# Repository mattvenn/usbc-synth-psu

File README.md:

# USBC Synth PSU

* uses STUSB4500 to negotiate 12v or 15v from a USBC power bank
* uses 4 [DC/DC switchers](https://www.ti.com/product/TPS56339) to supply 12, 9, 5 and 3v outputs for my various synths
* resistors can be changed to set different output voltage
* JP1 can be bridged and 12v DC/DC components not placed if power bank can supply 12v.

[PDF schematic](schematic.pdf)

[gerbers](synth-psu-2020-09-01-fab.zip)

[bom](synth-psu-bom.csv)

# Project log

For build notes, problems and fixes, please check the [project log](docs/log.md)

# Errata

* hole size is 5.3mm, should be 6 for M5 - fixed in PCB, not in gerbers

# Future improvements

* make the switcher parts snap-offable

# Resources

* proposed USBC charger: https://www.amazon.es/AUKEY-10000-mAh-Delivery-3-0-Cargador-Port%C3%A1til/dp/B07B4RQ47B/ref=sr_1_4?ascsubtag=UUacUdUnU67894YYwYg&dchild=1&keywords=AUKEY+USB+C+Power+Bank+10000mAh%2C+PD+Power+Bank+Slimline+with+18W+PD&linkCode=gs3&qid=1598631552&sr=8-4&tag=androcentr0f-21
* STUSB4500 datasheet https://www.st.com/en/interfaces-and-transceivers/stusb4500.html
* sparkfun USB PD product https://www.sparkfun.com/products/15801
* tindie USB PD product: https://github.com/oxplot/fabpide2
* sparkfun how to use their PD board: https://learn.sparkfun.com/tutorials/power-delivery-board---usb-c-qwiic-hookup-guide?_ga=2.100271642.500100063.1599656815-1406600584.1576753580

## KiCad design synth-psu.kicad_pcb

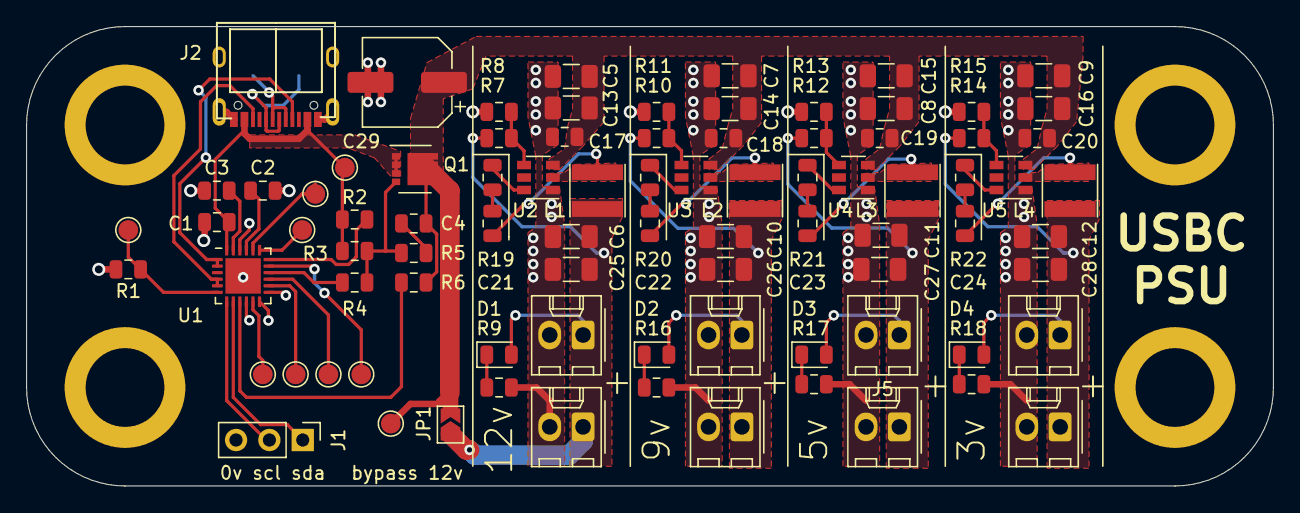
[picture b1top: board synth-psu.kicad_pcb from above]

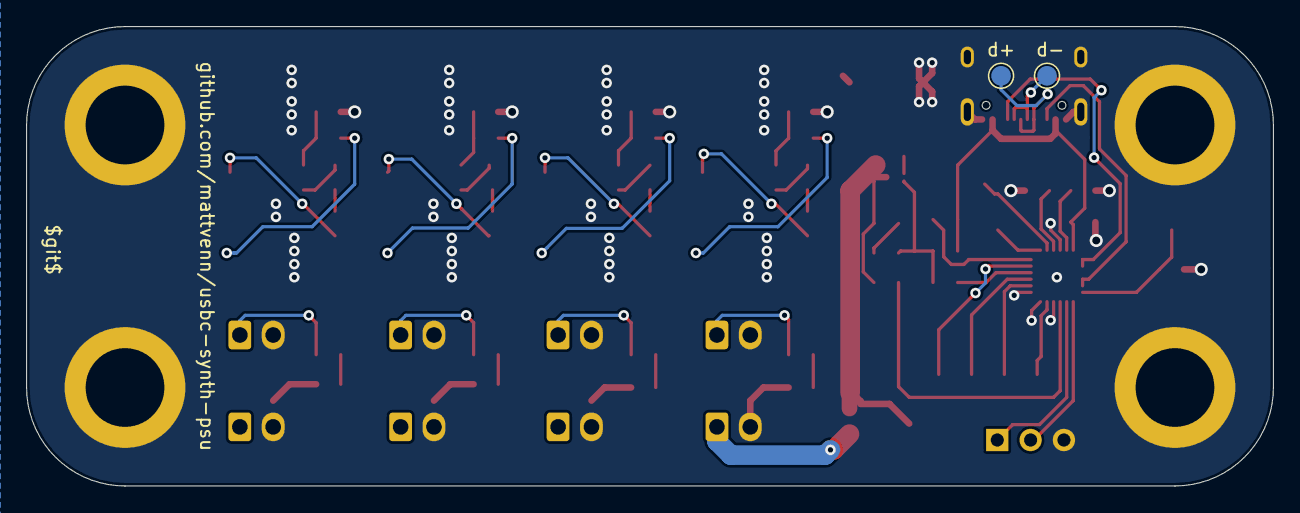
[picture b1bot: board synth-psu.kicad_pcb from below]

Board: 2 copper layers, 95.0 x 35.0 mm, 91 parts (2 on the bottom side), 47 nets.

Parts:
C1, C2, C3: 1uF; C_0805_2012Metric
C4, C17, C18, C19, C20, C21, C22, C23, C24: 100n; C_0805_2012Metric
C5, C7, C8, C9, C13, C14, C15, C16: 10u 25v; C_1206_3216Metric
C6, C10, C11, C12, C25, C26, C27, C28: 22u 16v; C_1206_3216Metric
C29: 100uf 25v; CP_Elec_6.3x5.9
D1, D2, D3, D4: LED; LED_0805_2012Metric
H1, H2, H3, H4: MountingHole_Pad; MountingHole_5.3mm_M5_DIN965_Pad
J1: Conn_01x03_Male; PinHeader_1x03_P2.54mm_Vertical
J2: USB_C_Receptacle_16pin; usb-c-16smt
J3, J4, J5, J6, J7, J8, J9, J10: Conn_01x02_Male; Molex_KK-254_AE-6410-02A_1x02_P2.54mm_Vertical
JP1: SolderJumper_2_Open; SolderJumper-2_P1.3mm_Open_TrianglePad1.0x1.5mm
L1, L2, L3, L4: 6.8uH; L_Taiyo-Yuden_NR-40xx
Q1: Q_PMOS_DSG; VSON-8_3.3x3.3mm_P0.65mm_NexFET
R1, R3, R10: 100k; R_0805_2012Metric
R2, R6: 1k; R_0805_2012Metric
R4: 22k; R_0805_2012Metric
R5, R18: 100r; R_0805_2012Metric
R7: 140k; R_0805_2012Metric
R8, R11, R13, R15: 10k; R_0805_2012Metric
R9: 660r; R_0805_2012Metric
R12: 51k; R_0805_2012Metric
R14: 27.4k; R_0805_2012Metric
R16: 470r; R_0805_2012Metric
R17: 200r; R_0805_2012Metric
R19, R20, R21, R22: 30R; R_0805_2012Metric
TP1, TP2, TP3, TP4, TP5, TP6, TP7, TP8, TP9, TP10, TP11: TestPoint; TestPoint_Pad_D1.5mm
U1: STUSB4500QTR; QFN-24-1EP_4x4mm_P0.5mm_EP2.7x2.7mm
U2, U3, U4, U5: TPS56339; SOT-23-6

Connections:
+1V2: C2.1, U1.21
+2V8: C3.1, U1.23
+3V0: C12.1, C28.1, D4.2, J6.1, J10.1, L4.2, R14.2
+5V: C11.1, C27.1, D3.2, J5.1, J9.1, L3.2, R12.2
+9V: C10.1, C26.1, D2.2, J4.1, J8.1, L2.2, R10.2
+12V: C6.1, C25.1, D1.2, J3.1, J7.1, JP1.1, L1.2, R7.2
+15V: C4.1, C5.1, C7.1, C8.1, C9.1, C13.1, C14.1, C15.1, C16.1, C17.1, C18.1, C19.1, C20.1, C29.1, JP1.2, Q1.5, R6.2, TP8.1, U2.3, U3.3, U4.3, U5.3
/cc1: J2.A5, U1.1, U1.2
/cc2: J2.B5, U1.4, U1.5
/d+: J2.A6, J2.B6, TP11.1
/d-: J2.A7, J2.B7, TP10.1
/disch: R6.1, U1.9
/scl: J1.2, U1.7
/sda: J1.1, U1.8
/sw_3: C24.2, L4.1, U5.2
/sw_5: C23.2, L3.1, U4.2
/sw_9: C22.2, L2.1, U3.2
/sw_12v: C21.2, L1.1, U2.2
/vbus_en_sink: R4.2, U1.16
/vbus_vs_disch: R2.2, U1.18
Earth: C1.2, C2.2, C3.2, C5.2, C6.2, C7.2, C8.2, C9.2, C10.2, C11.2, C12.2, C13.2, C14.2, C15.2, C16.2, C17.2, C18.2, C19.2, C20.2, C25.2, C26.2, C27.2, C28.2, C29.2, H1.1, H2.1, H3.1, H4.1, J1.3, J2.A1/B12, J2.B1/A12, J2.S1, J2.S2, J2.S3, J2.S4, J3.2, J4.2, J5.2, J6.2, J7.2, J8.2, J9.2, J10.2, R1.2, R8.1, R9.1, R11.1, R13.1, R15.1, R16.1, R17.1, R18.1, U1.10, U1.12, U1.13, U1.22, U1.25, U2.1, U3.1, U4.1, U5.1
unnamed: C4.2, R5.1
unnamed: C21.1, R19.2
unnamed: C22.1, R20.2
unnamed: C23.1, R21.2
unnamed: C24.1, R22.2
unnamed: D1.1, R9.2
unnamed: D2.1, R16.2
unnamed: D3.1, R17.2
unnamed: D4.1, R18.2
unnamed: Q1.4, R3.2, R4.1, R5.2
unnamed: R1.1, TP7.1, U1.6
unnamed: R7.1, R8.2, U2.4
unnamed: R10.1, R11.2, U3.4
unnamed: R12.1, R13.2, U4.4
unnamed: R14.1, R15.2, U5.4
unnamed: R19.1, U2.6
unnamed: R20.1, U3.6
unnamed: R21.1, U4.6
unnamed: R22.1, U5.6
unnamed: TP1.1, U1.19
unnamed: TP2.1, U1.20
unnamed: TP3.1, U1.14
unnamed: TP4.1, U1.17
unnamed: TP5.1, U1.11
unnamed: TP6.1, U1.15
VBUS: C1.1, J2.A4/B9, J2.B4/A9, Q1.1, Q1.2, Q1.3, R2.1, R3.1, TP9.1, U1.24

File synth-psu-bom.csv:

"Ref","Qnty","Value","Cmp name","Manufacturer","Partnum"
"C1, C2, C3, ","3","1uF","C","Kemet","C0805C105K3PACTU"
"C4, C17, C18, C19, C20, C21, C22, C23, C24, ","9","100n","C","Kemet","C0805C104Z3VACTU"
"C5, C7, C8, C9, C13, C14, C15, C16, ","8","10u 25v","C","Multicomp","MC1206X106K250CT"
"C6, C10, C11, C12, C25, C26, C27, C28, ","8","22u 16v","C","Kemet","C1206C226M4PACTU"
"C29, ","1","100uf 25v","CP","Panasonic","EEEFKE101XAP"
"D1, D2, D3, D4, ","4","LED","LED","Kingbright","KPT-2012EC "
"H1, H2, H3, H4, ","4","MountingHole_Pad","MountingHole_Pad","",""
"J1, ","1","Conn_01x03_Male","Conn_01x03_Male","",""
"J2, ","1","USB_C_Receptacle_16pin","USB_C_Receptacle_16pin","",""
"J3, J4, J5, J6, J7, J8, J9, J10, ","8","Conn_01x02_Male","Conn_01x02_Male","Molex","22-23-2021"
"JP1, ","1","SolderJumper_2_Open","SolderJumper_2_Open","",""
"L1, L2, L3, L4, ","4","6.8uH","L","Vishay","IFSC1515AHER6R8M01"
"Q1, ","1","Q_PMOS_DSG","Q_PMOS_DSG","ST","STL6P3LLH6"
"R1, R3, R10, ","3","100k","R","Multicomp","MCWR08X1003FTL"
"R2, R6, ","2","1k","R","Multicomp","MCMR08X1001FTL "
"R4, ","1","22k","R","Multicomp","MCWR08X2202FTL "
"R5, R18, ","2","100r","R","Multicomp","MCWR08X1000FTL "
"R7, ","1","140k","R","Multicomp","MCWR08X1403FTL "
"R8, R11, R13, R15, ","4","10k","R","Multicomp","MCMR08X1002FTL"
"R9, ","1","660r","R","Multicomp","MCMR08X6650FTL "
"R12, ","1","51k","R","Multicomp","MCWR08X5102FTL "
"R14, ","1","27.4k","R","Multicomp","MCMR08X2742FTL"
"R16, ","1","470r","R","Multicomp","MCWR08X4700FTL "
"R17, ","1","200r","R","Multicomp","MCWR08X2000FTL "
"R19, R20, R21, R22, ","4","30R","R","Multicomp","MCWR08X30R0FTL "
"TP1, TP2, TP3, TP4, TP5, TP6, TP7, TP8, TP9, TP10, TP11, ","11","TestPoint","TestPoint","",""
"U1, ","1","STUSB4500QTR","STUSB4500QTR","ST","STUSB4500QTR "
"U2, U3, U4, U5, ","4","TPS56339","TPS562200","Texas Instruments","TPS56339DDCR"

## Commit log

2020-08-30 notes
2020-08-31 footprints and initial layout
2020-08-31 more notes
2020-08-31 need to find a new dc/dc. also allow bypass of 12v switcher
2020-08-31 neaten schematic and export board pic and schematic pic
2020-08-31 alternative switcher
2020-08-31 mosfet footprint and lib, routed stusb4500
2020-08-31 part number for mosfet
2020-09-01 add fft of po audio out
2020-09-01 fft pic
2020-09-01 change dc/dc to new part and did layout
2020-09-01 removed 1 set of supply sockets to fit molex polarised kk, silk screen
2020-09-01 led resistors
2020-09-01 updated todos
2020-09-01 gerbers
2020-09-01 fixed silk overlap on +
2020-09-01 add gerber link to readme
2020-09-01 updated board pic
2020-09-01 updated schematic
2020-09-01 fix part number on dc switchers
2020-09-01 link to switcher
2020-09-01 more neatening
2020-09-01 shortened vfb traces
2020-09-01 reexport gerber
2020-09-01 continue tweaking dc/dc copper pours
2020-09-01 add vbus testpoint
2020-09-01 auto export config file
2020-09-02 bom wip
2020-09-02 usb test pads, add some component order codes, check sizes of caps
2020-09-02 usb test pads
2020-09-02 remove old files
2020-09-02 ordered pcbs
2020-09-02 part numbers
2020-09-02 bom link
2020-09-09 platformio config
2020-09-09 ignore
2020-09-09 link and instructions for fw
2020-09-10 push through bom changes to the pcb for the interactive bom viewer
2020-09-10 fw updates to only ask for 12v
2020-09-10 bring up notes
2020-09-10 fixed mount holes to 6mm
2020-09-14 9v switcher test results
2020-09-14 format
2020-09-14 add 1000mA test
2020-09-15 noise investigation
2020-09-15 note on range of filter
2020-09-16 reduce lower voltage level to 10v (16%)
2020-09-16 split out log into separate file
2021-08-03 updates about serial mon, improvement
2021-08-03 kicad5
2021-08-04 working for 9v out
2021-08-04 notes on 9v supply
